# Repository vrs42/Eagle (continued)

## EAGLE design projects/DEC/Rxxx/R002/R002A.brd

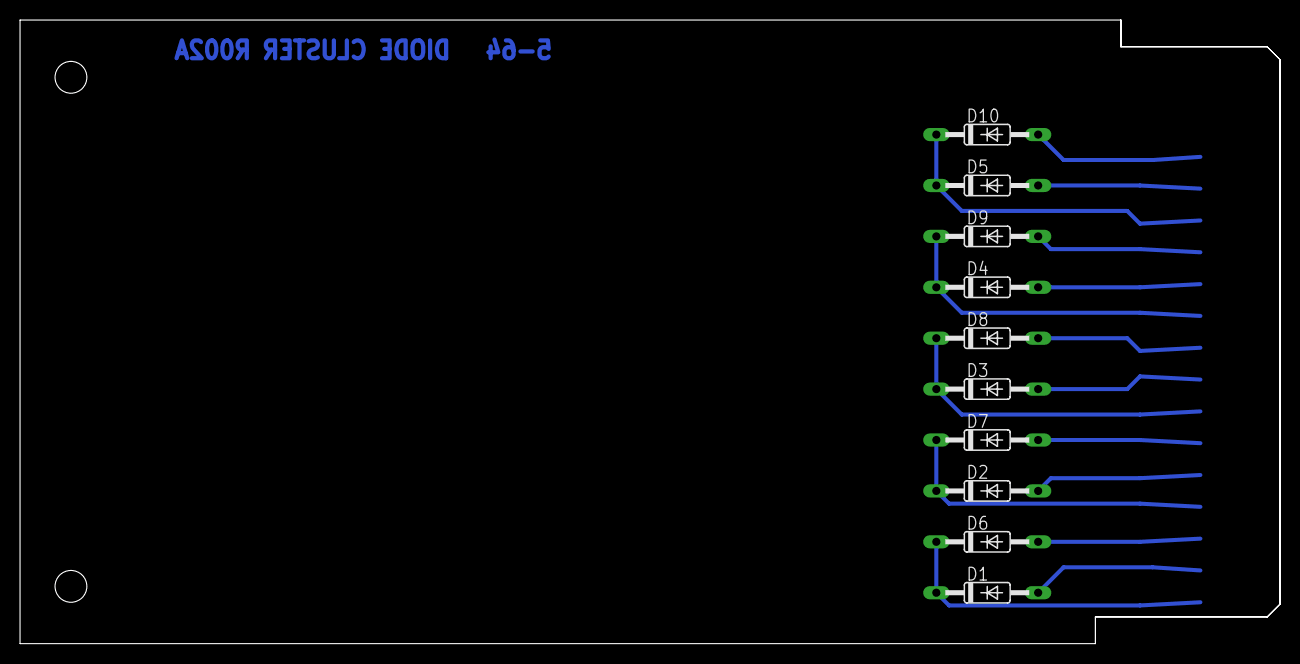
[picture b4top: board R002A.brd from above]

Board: 2 copper layers, 125.7 x 62.2 mm, 12 parts (0 on the bottom side), 15 nets.

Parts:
D1, D2, D3, D4, D5, D6, D7, D8, D9, D10: 1N3606; DO35-10
U$1: OUTLINE-SINGLE; SINGLE
U$2: EDGE-1; EDGE-CON1

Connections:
unnamed: D10.A, U$2.D2
unnamed: D5.A, U$2.E2
unnamed: D5.C, D10.C, U$2.F2
unnamed: D9.A, U$2.H2
unnamed: D4.A, U$2.J2
unnamed: D4.C, D9.C, U$2.K2
unnamed: D8.A, U$2.L2
unnamed: D3.A, U$2.M2
unnamed: D3.C, D8.C, U$2.N2
unnamed: D7.A, U$2.P2
unnamed: D2.A, U$2.R2
unnamed: D2.C, D7.C, U$2.S2
unnamed: D6.A, U$2.T2
unnamed: D1.A, U$2.U2
unnamed: D1.C, D6.C, U$2.V2
